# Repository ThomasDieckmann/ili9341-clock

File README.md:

# Uhr mit ILI9341 display

Das war eigentlich eine schnelle Bastelei, die auch zugegebenermaßen noch nicht ganz fertig ist.
So sieht der Code allerdings auch aus. Da könnten irgendwann noch einmal ein paar Kommentare hinein.

Hinweise:
- Viele dieser LCD-Displays kommen als 3,3V-Version ohne Pegelwandler auf den Markt. Daher habe ich
  im Schaltplan die Spannungsteiler eingesetzt. Sollten Pegelwandler verbaut sein, kann der Spannungsteiler
  entfallen und das Display direkt angeschlossen werden.
- Dass alle Segmente gezeichnet werden, ist gewollt. Die inaktiven Segmente werden in einer dunkleren
  Farbe dargestellt, damit der Eindruck eines 7-Segment LED-Displays entsteht. Wen's stört, der kann
  das im Code gerne auf schwarz stellen.

TODO:
- Integration LDR im Code => Steuern LED Hintergrundbeleuchtung
- Alarmfunktion
- Chime-Funktion
- präziseres RTC-Modul finden

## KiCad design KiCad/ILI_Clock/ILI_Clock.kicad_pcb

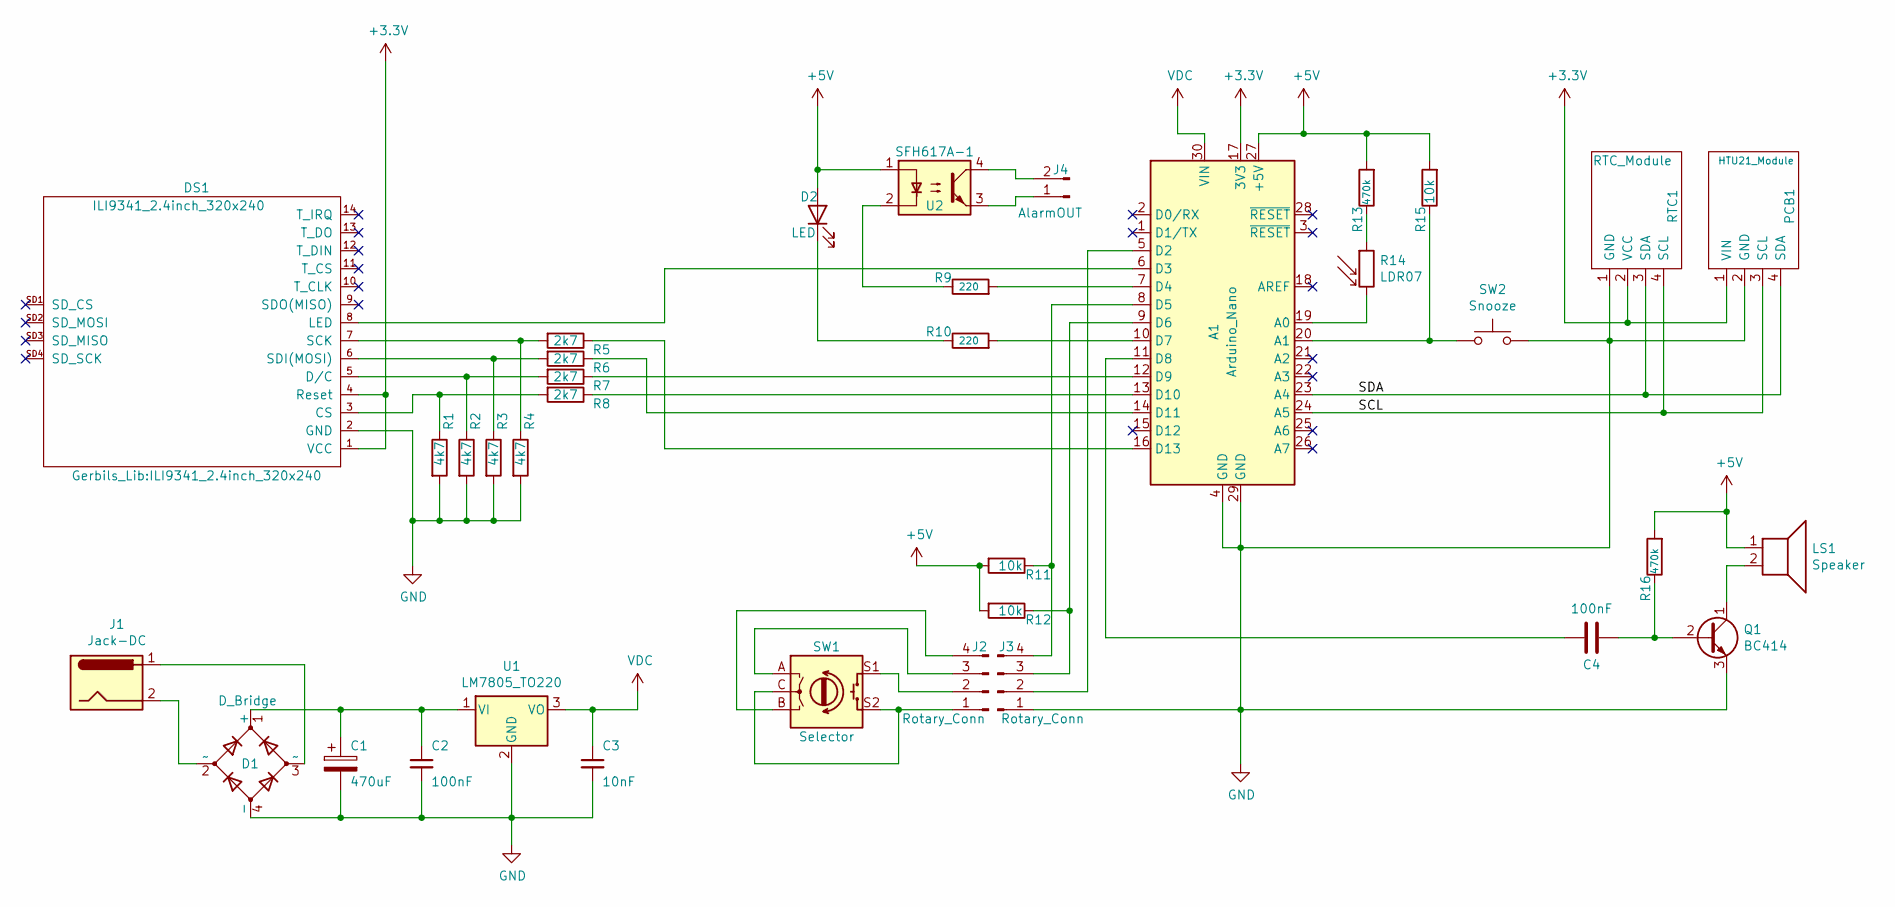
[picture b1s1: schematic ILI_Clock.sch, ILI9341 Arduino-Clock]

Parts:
A1: Arduino_Nano
C1: 470uF; CP_Radial_D8.0mm_P5.00mm
C2: 100nF; C_Axial_L3.8mm_D2.6mm_P10.00mm_Horizontal
C3: 10nF; C_Axial_L3.8mm_D2.6mm_P10.00mm_Horizontal
C4: 100nF; C_Axial_L5.1mm_D3.1mm_P10.00mm_Horizontal
D1: D_Bridge; Diode_Bridge_Round_D9.8mm
D2: LED; PinHeader_1x02_P2.54mm_Vertical
DS1: ILI9341_2.4inch_320x240
J1: Jack-DC; BarrelJack_CUI_PJ-063AH_Horizontal_CircularHoles
J2, J3: Rotary_Conn; PinHeader_1x04_P2.54mm_Vertical
J4: AlarmOUT; PinHeader_1x02_P2.54mm_Vertical
LS1: Speaker; Buzzer_TDK_PS1240P02BT_D12.2mm_H6.5mm
PCB1: HTU21_Module; HTU21
Q1: BC414; TO-92_Inline
R1, R2, R3, R4: 4k7; R_Axial_DIN0411_L9.9mm_D3.6mm_P12.70mm_Horizontal
R5, R6, R7, R8: 2k7; R_Axial_DIN0411_L9.9mm_D3.6mm_P12.70mm_Horizontal
R9, R10: 220; R_Axial_DIN0411_L9.9mm_D3.6mm_P12.70mm_Horizontal
R11, R12, R15: 10k; R_Axial_DIN0411_L9.9mm_D3.6mm_P12.70mm_Horizontal
R13, R16: 470k; R_Axial_DIN0411_L9.9mm_D3.6mm_P12.70mm_Horizontal
R14: LDR07; R_LDR_5.1x4.3mm_P3.4mm_Vertical
RTC1: RTC_Module; PinHeader_1x04_P2.54mm_Vertical
SW1: Selector; RotaryEncoder_Alps_EC11E-Switch_Vertical_H20mm
SW2: Snooze; PinHeader_1x02_P2.54mm_Vertical
U1: LM7805_TO220; TO-220-3_Horizontal_TabDown
U2: SFH617A-1; DIP-4_W7.62mm

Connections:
+3V3: A1.17 (3V3), DS1.1 (VCC), DS1.4 (Reset), PCB1.1 (VIN), RTC1.2 (VCC)
+5V: A1.27 (+5V), D2.2 (A), LS1.1, R11.2, R12.2, R13.2, R15.2, R16.2, U2.1
/SCL: A1.24 (A5), PCB1.3 (SCL), RTC1.4 (SCL)
/SDA: A1.23 (A4), PCB1.4 (SDA), RTC1.3 (SDA)
GND: A1.4 (GND), A1.29 (GND), C1.2, C2.2, C3.2, D1.4 (-), DS1.2 (GND), J3.1, PCB1.2 (GND), Q1.3 (E), R1.2, R2.2, R3.2, R4.2, RTC1.1 (GND), SW2.2, U1.2 (GND)
unnamed: A1.5 (D2), J3.2
unnamed: A1.6 (D3), DS1.8 (LED)
unnamed: A1.7 (D4), R9.2
unnamed: A1.8 (D5), J3.4, R11.1
unnamed: A1.9 (D6), J3.3, R12.1
unnamed: A1.10 (D7), R10.2
unnamed: A1.11 (D8), C4.2
unnamed: A1.12 (D9), R7.1
unnamed: A1.13 (D10), R8.1
unnamed: A1.14 (D11), R6.1
unnamed: A1.16 (D13), R5.1
unnamed: A1.19 (A0), R14.2
unnamed: A1.20 (A1), R15.1, SW2.1
unnamed: C1.1, C2.1, D1.1 (+), U1.1 (VI)
unnamed: C4.1, Q1.2 (B), R16.1
unnamed: D1.2 (~~), J1.2
unnamed: D1.3 (~~), J1.1
unnamed: D2.1 (K), R10.1
unnamed: DS1.3 (CS), R1.1, R8.2
unnamed: DS1.5 (D/C), R2.1, R7.2
unnamed: DS1.6 (SDI(MOSI)), R3.1, R6.2
unnamed: DS1.7 (SCK), R4.1, R5.2
unnamed: J2.1, SW1.C, SW1.S2
unnamed: J2.2, SW1.S1
unnamed: J2.3, SW1.A
unnamed: J2.4, SW1.B
unnamed: J4.1, U2.3
unnamed: J4.2, U2.4
unnamed: LS1.2, Q1.1 (C)
unnamed: R9.1, U2.2
unnamed: R13.1, R14.1
VDC: A1.30 (VIN), C3.1, U1.3 (VO)

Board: 2 copper layers, 36 parts (0 on the bottom side), 37 nets, no tracks yet.

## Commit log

2026-06-26 Add GNU General Public License v3
    Added the GNU General Public License version 3 to the project.
2026-06-26 Add initial content to leer.datei
2026-06-26 Add files via upload
    Initial upload of source code
2026-06-26 Create leer
2026-06-26 Create mt
2026-06-26 Create README.md for Uhr project
    Added initial README content for Uhr project with notes and TODOs.
2026-06-26 Add TODO item for finding a more precise RTC module
